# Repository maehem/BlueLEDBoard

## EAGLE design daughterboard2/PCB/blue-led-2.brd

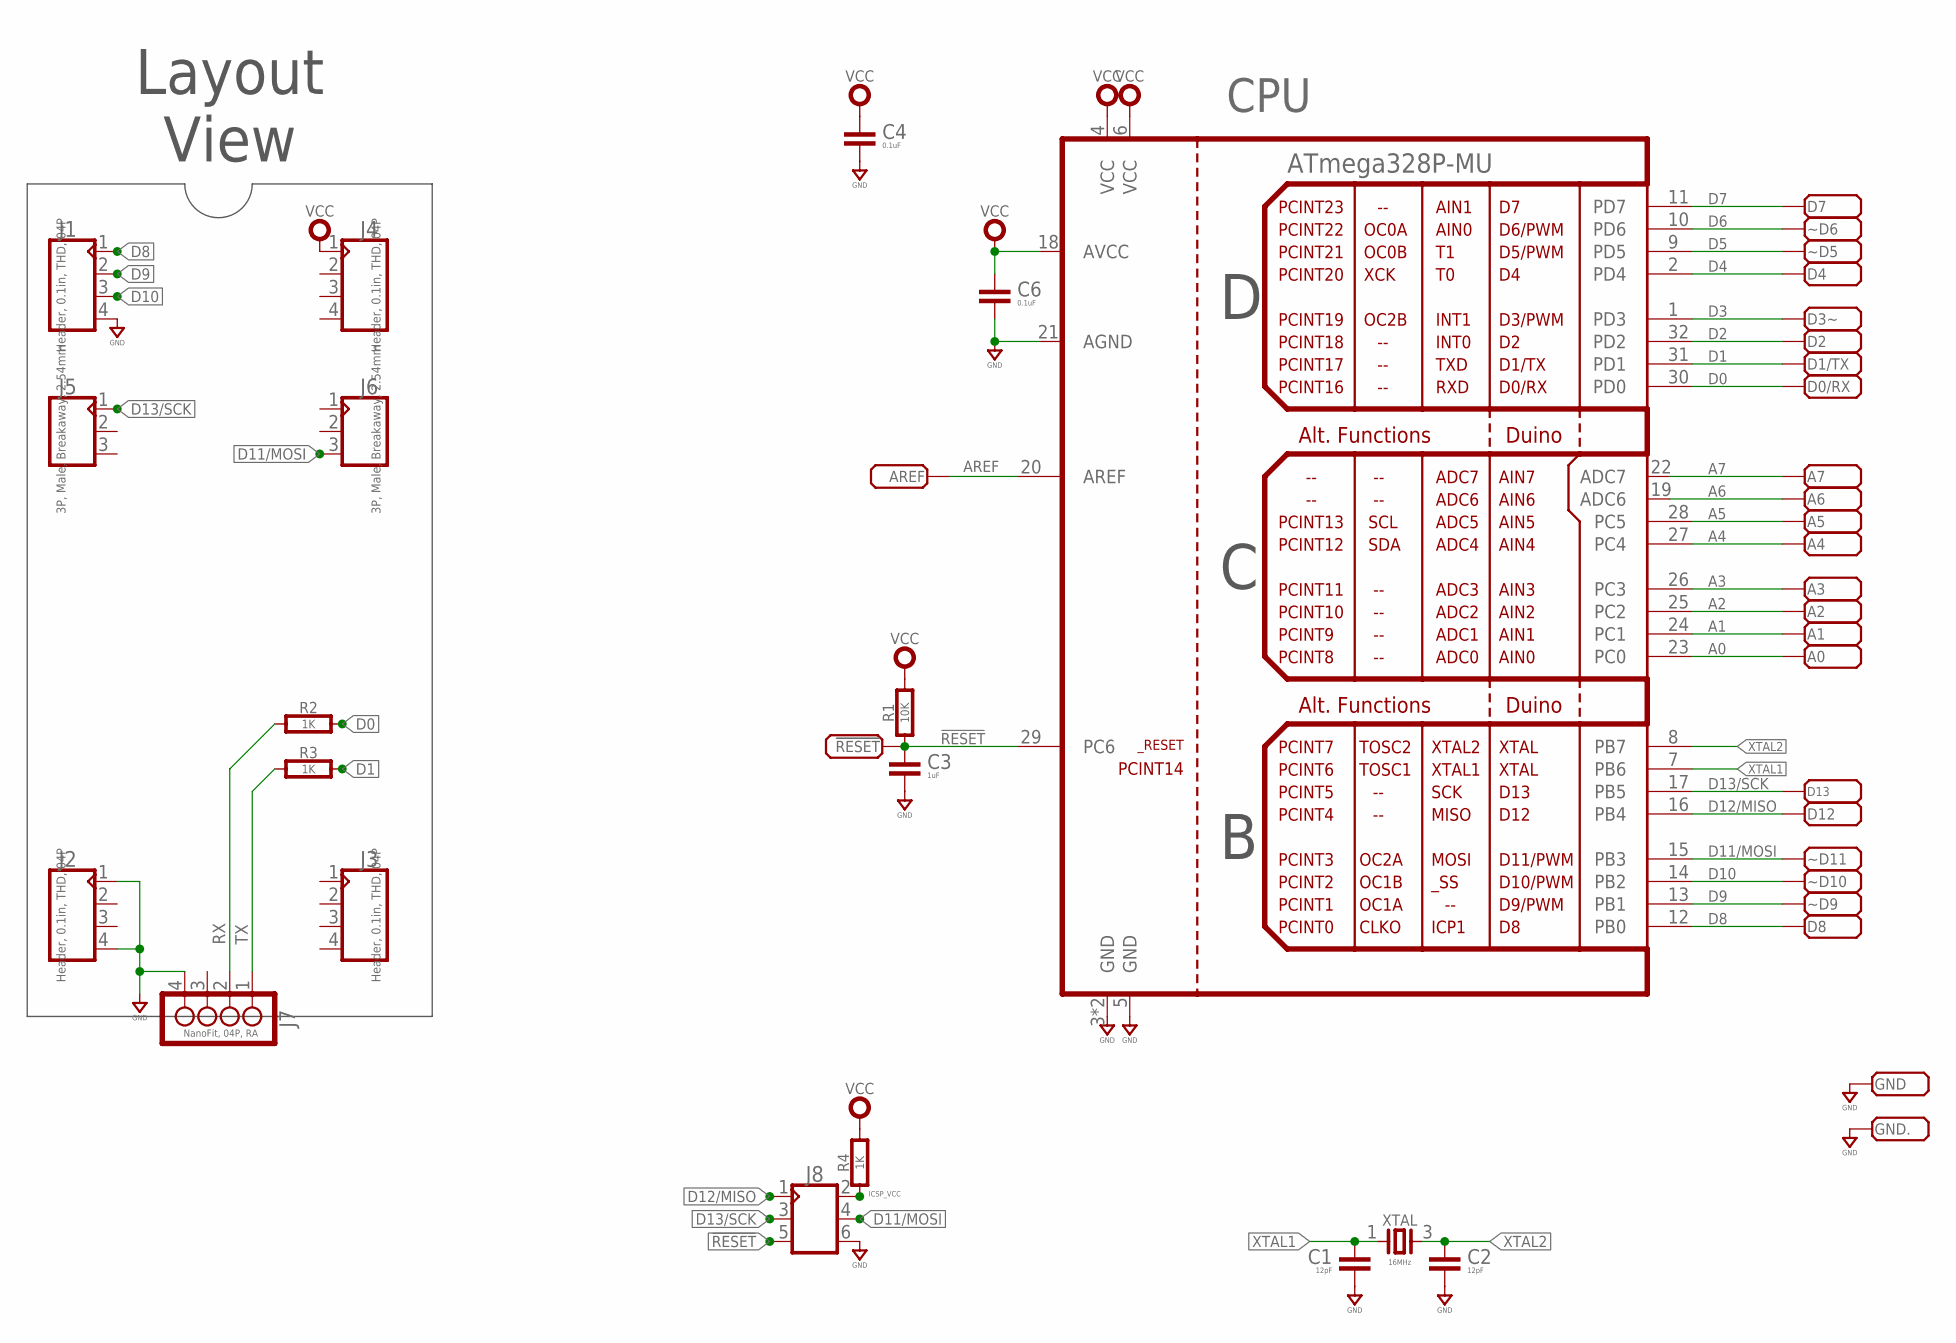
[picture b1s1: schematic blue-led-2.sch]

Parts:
!RESET: PADSMD-050X050; SMD-050X050
A0, A1, A2, A3, A4, A5, A6, A7: PADSMD-050X050; SMD-050X050
AREF: PADSMD-050X050; SMD-050X050
C1, C2: 12pF; 0603-CAP
C3: 1uF; 0603-CAP
C4, C6: 0.1uF; 0603-CAP
CPU: ATmega328P-MU; MLF32
D0/RX, D1/TX, D2, D3~, D4, D7, D8, D12, D13: PADSMD-050X050; SMD-050X050
GND, GND.: PADSMD-050X050; SMD-050X050
J1, J2, J3, J4: Header, 0.1in, THD, 04P; MA04X1-VT-THD
J5, J6: 3P, Male, Breakaway, 2.54mm; MA03X1-VT-THD
J7: NanoFit, 04P, RA; MOLEX-105313-XX04
J8: CON_03X2-VT_SMD; MA03X2-VT-SMD
R1: 10K; 0603-RES
R2, R3, R4: 1K; 0603-RES
XTAL: 16MHz; 32X25
~D5, ~D6, ~D9, ~D10, ~D11: PADSMD-050X050; SMD-050X050

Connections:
!RESET: !RESET.1, C3.1, CPU.29 (PC6), J8.5, R1.1
A0: A0.1, CPU.23 (PC0)
A1: A1.1, CPU.24 (PC1)
A2: A2.1, CPU.25 (PC2)
A3: A3.1, CPU.26 (PC3)
A4: A4.1, CPU.27 (PC4)
A5: A5.1, CPU.28 (PC5)
A6: A6.1, CPU.19 (ADC6)
A7: A7.1, CPU.22 (ADC7)
AREF: AREF.1, CPU.20 (AREF)
D0: CPU.30 (PD0), D0/RX.1, R2.2
D1: CPU.31 (PD1), D1/TX.1, R3.2
D2: CPU.32 (PD2), D2.1
D3: CPU.1 (PD3), D3~.1
D4: CPU.2 (PD4), D4.1
D5: CPU.9 (PD5), ~D5.1
D6: CPU.10 (PD6), ~D6.1
D7: CPU.11 (PD7), D7.1
D8: CPU.12 (PB0), D8.1, J1.1
D9: CPU.13 (PB1), J1.2, ~D9.1
D10: CPU.14 (PB2), J1.3, ~D10.1
D11/MOSI: CPU.15 (PB3), J6.3, J8.4, ~D11.1
D12/MISO: CPU.16 (PB4), D12.1, J8.1
D13/SCK: CPU.17 (PB5), D13.1, J5.1, J8.3
GND: C1.2, C2.2, C3.2, C4.2, C6.2, CPU.3 (GND), CPU.5 (GND), CPU.21 (AGND), CPU.PAD (GND), GND.1, GND..1, J1.4, J2.1, J2.4, J7.4, J8.6
ICSP_VCC: J8.2, R4.1
RX: J7.2, R2.1
TX: J7.1, R3.1
VCC: C4.1, C6.1, CPU.4 (VCC), CPU.6 (VCC), CPU.18 (AVCC), J4.1, R1.2, R4.2
XTAL1: C1.1, CPU.7 (PB6), XTAL.1
XTAL2: C2.1, CPU.8 (PB7), XTAL.3

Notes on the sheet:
Layout View

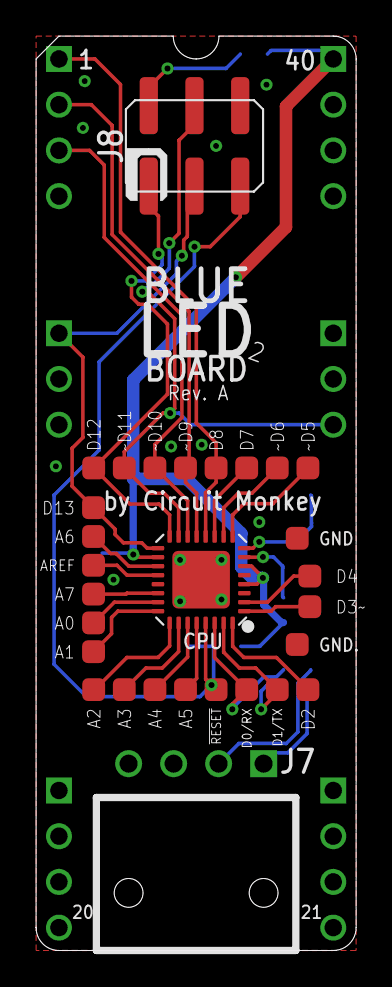
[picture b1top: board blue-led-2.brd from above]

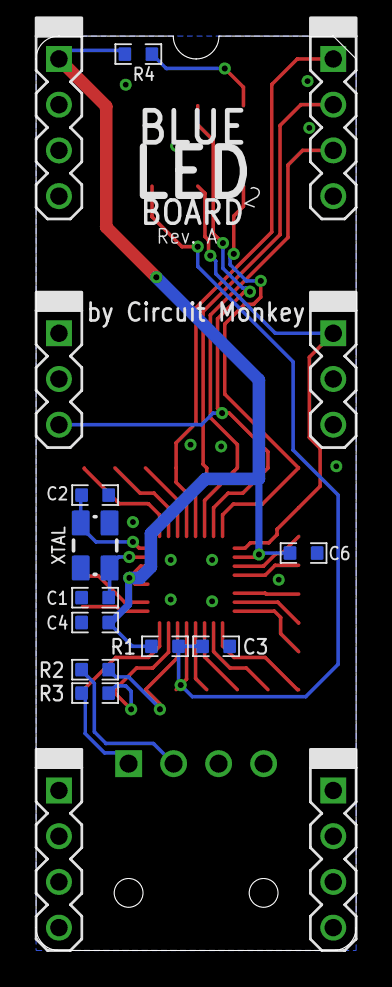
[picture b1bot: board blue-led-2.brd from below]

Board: 2 copper layers, 17.8 x 50.8 mm, 45 parts (16 on the bottom side), 31 nets.

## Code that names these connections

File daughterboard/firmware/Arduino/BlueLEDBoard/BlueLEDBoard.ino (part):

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// Drive BlueMan LED controller board


// COL DATA   - MOSI - PB3 - Chip pin 17 - Arduino Pin 11 - Board IC1 pin 32
// COL CLOCK  - SCK  - PB5 - Chip pin 19 - Arduino pin 13 - Board IC1 pin  7

// ROW SELECT - PB0-PB2 - Chip pins 14-16 - Arduino pins 8-10 - Board IC1 pins 1-3

// NOTE: ROW SELECT #3 is hardwired to ground on the daughter board
// NOTE: code assumes it is ok to directly assign row to full 8 bits of PB even though only bottom 3 bits are used
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
#define DDR_SPI DDRB
#define PORT_SPI PORTB
#define DD_MOSI 3     // PB3 = Pin 17 = Digital 11
#define DD_SCK  5     // PB5 = Pin 19 = Digital 13
#define DD_SS   2     // PB2 = Pin 16 = Digital 10

// "19.3.2: If SS is configured as an output, the pin is a general output pin which does not affect the SPI system."
// So we must keep SS output, but can be generally used.
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
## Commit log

2022-05-17 Changes made for BMG 2022 upgrade.
2022-05-24 Merge original schematic for daughter board.
    Pulled from other archive location.
2022-05-27 Format party!
    Previous code was double and triple spaced. Made code unreadable.
2022-05-28 Clean up code formatting.
2022-05-28 Change wait time to check stick status.
2022-05-28 Update message to reference USB stick.
2022-05-28 Add code comments.
2022-05-28 Code formatting. Fewer crosshatches.
2022-05-28 Create USB drive template with written instructions.
2022-05-28 Change how files are referenced.
2022-05-29 Update descriptions and git-ignore of some PCB CAD files.
2022-05-30 Rev.A pre-fab. final?
2022-05-30 PDF version of BOM
2022-05-31 Debug comments were filling log.
2022-06-02 Fix installer issue.
2022-06-02 Add comments for future changes.
